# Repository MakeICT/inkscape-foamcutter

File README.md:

MakeICT Foam Cutter Serial Export tool for Inkscape
===================================================

This is an Inkscape extension that allows you to export your Inkscape drawings as G-Code through a serial port.

This project is a modified version of [http://github.com/martymcguire/inkscape-unicorn](http://github.com/martymcguire/inkscape-unicorn)

Installation
============

Inkscape
--------
Copy the contents of `inkscape/` to your Inkscape `extensions/` folder.
Typical locations include:

* Linux - `/usr/share/inkscape/extensions`
* Windows - `C:\Program Files\Inkscape\share\extensions`
* OS X - `/Applications/Inkscape.app/Contents/Resources/extensions`

You will also need pyserial installed to `inkscape/python/Lib` folder.

Arduino
-------
Upload the Arduino code from the `arduino/` folder. We highly recommend using [Ino Tool](http://inotool.org)

Usage
=====

* Size and locate your image appropriately:
	* It looks like only **px** are supported as the units presently
* Convert all text to paths:
	* Select all text objects.
	* Path > Object to Path.
* Export to serial
	* Extensions > Export > MakeICT Foam Cutter Sender.

Credits
=======

* Marty McGuire pulled this all together into an Inkscape extension.
* [Inkscape](http://www.inkscape.org/) is an awesome open source vector graphics app.
* [Scribbles](https://github.com/makerbot/Makerbot/tree/master/Unicorn/Scribbles%20Scripts) is the original DXF-to-Unicorn Python script.
* [The Egg-Bot Driver for Inkscape](http://code.google.com/p/eggbotcode/) provided inspiration and good examples for working with Inkscape's extensions API.
* Dominic Canare for adding serial code to Marty's original extension
* Tom McGuire for sharing his vast knowledge of G-Code and CNC.

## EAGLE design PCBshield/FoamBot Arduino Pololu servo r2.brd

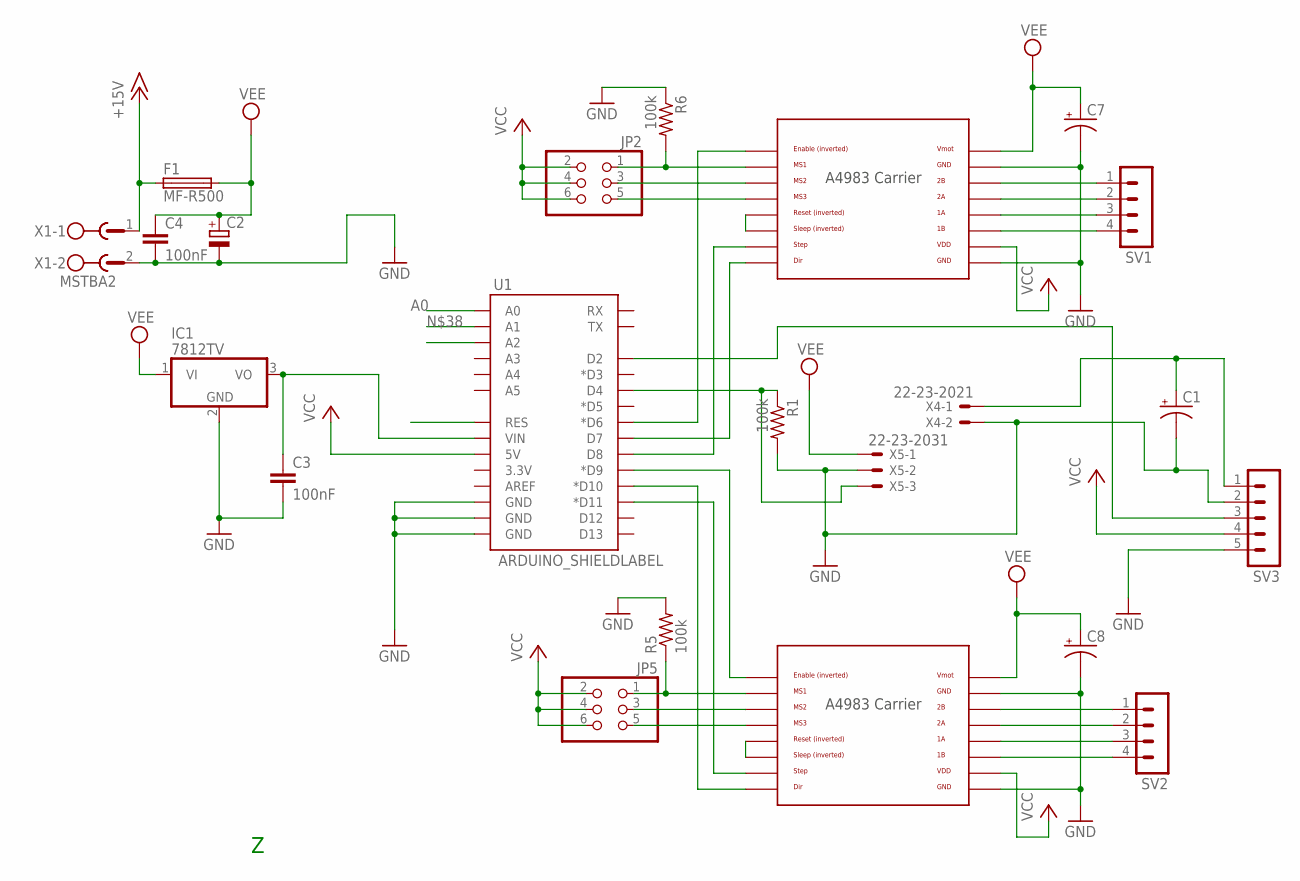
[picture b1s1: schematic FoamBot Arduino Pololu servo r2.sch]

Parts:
C1: CPOL-USE5-10.5; E5-10,5
C2: CPOL-EUE7.5-16; E7,5-16
C3, C4: 100nF; C2.5-3
C7, C8: CAP_POLPTH2; CPOL-RADIAL-10UF-25V
F1: MF-R500; LITTLEFUSE
IC1: 7812TV; TO220V
JP2, JP5: PINHD-2X3; 2X03
R1, R5, R6: 100k; 0207/7
SV1, SV2: MA04-1
SV3: MA05-1
U1: ARDUINO_SHIELDLABEL; DUEMILANOVE_SHIELD
U2, U3: POLOLU_A4983CARRIER; A4983CARRIER
X1: MSTBA2
X4: 22-23-2021
X5: 22-23-2031

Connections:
+15V: F1.1, X1.1
A0: U1.A0
GND: C1.-, C2.-, C3.2, C4.2, C7.2 (-), C8.2 (-), IC1.2 (GND), R1.2, R5.2, R6.1, SV3.2, SV3.5, U1.GND@0 (GND), U1.GND@1 (GND), U1.GND@2 (GND), U2.GND, U2.GND@0 (GND), U3.GND, U3.GND@0 (GND), X1.2, X4.2, X5.2
unnamed: U1.D8, U2.STEP
unnamed: U1.D7, U2.DIR
unnamed: SV1.1, U2.2B
unnamed: SV1.2, U2.2A
unnamed: JP5.1, R5.1, U3.MS1
unnamed: JP5.3, U3.MS2
unnamed: U2.RST, U2.SLP (SLEEP)
unnamed: C3.1, IC1.3 (VO), U1.VIN
unnamed: SV1.3, U2.1A
unnamed: SV1.4, U2.1B
unnamed: SV2.4, U3.1B
unnamed: U1.D6 (*D6), U2.EN
unnamed: JP5.5, U3.MS3
unnamed: JP2.1, R6.2, U2.MS1
unnamed: U1.D11 (*D11), U3.STEP
unnamed: U1.D10 (*D10), U3.DIR
unnamed: JP2.3, U2.MS2
unnamed: JP2.5, U2.MS3
unnamed: U3.RST, U3.SLP (SLEEP)
unnamed: SV2.1, U3.2B
unnamed: SV2.2, U3.2A
unnamed: U1.D9 (*D9), U3.EN
unnamed: R1.1, U1.D4, X5.3
unnamed: SV3.3, U1.D2
unnamed: SV2.3, U3.1A
unnamed: C1.+, SV3.1, X4.1
RESET: U1.RES
VCC: JP2.2, JP2.4, JP2.6, JP5.2, JP5.4, JP5.6, SV3.4, U1.5V, U2.VDD, U3.VDD
VEE: C2.+, C4.1, C7.1 (+), C8.1 (+), F1.2, IC1.1 (VI), U2.VMOT, U3.VMOT, X5.1

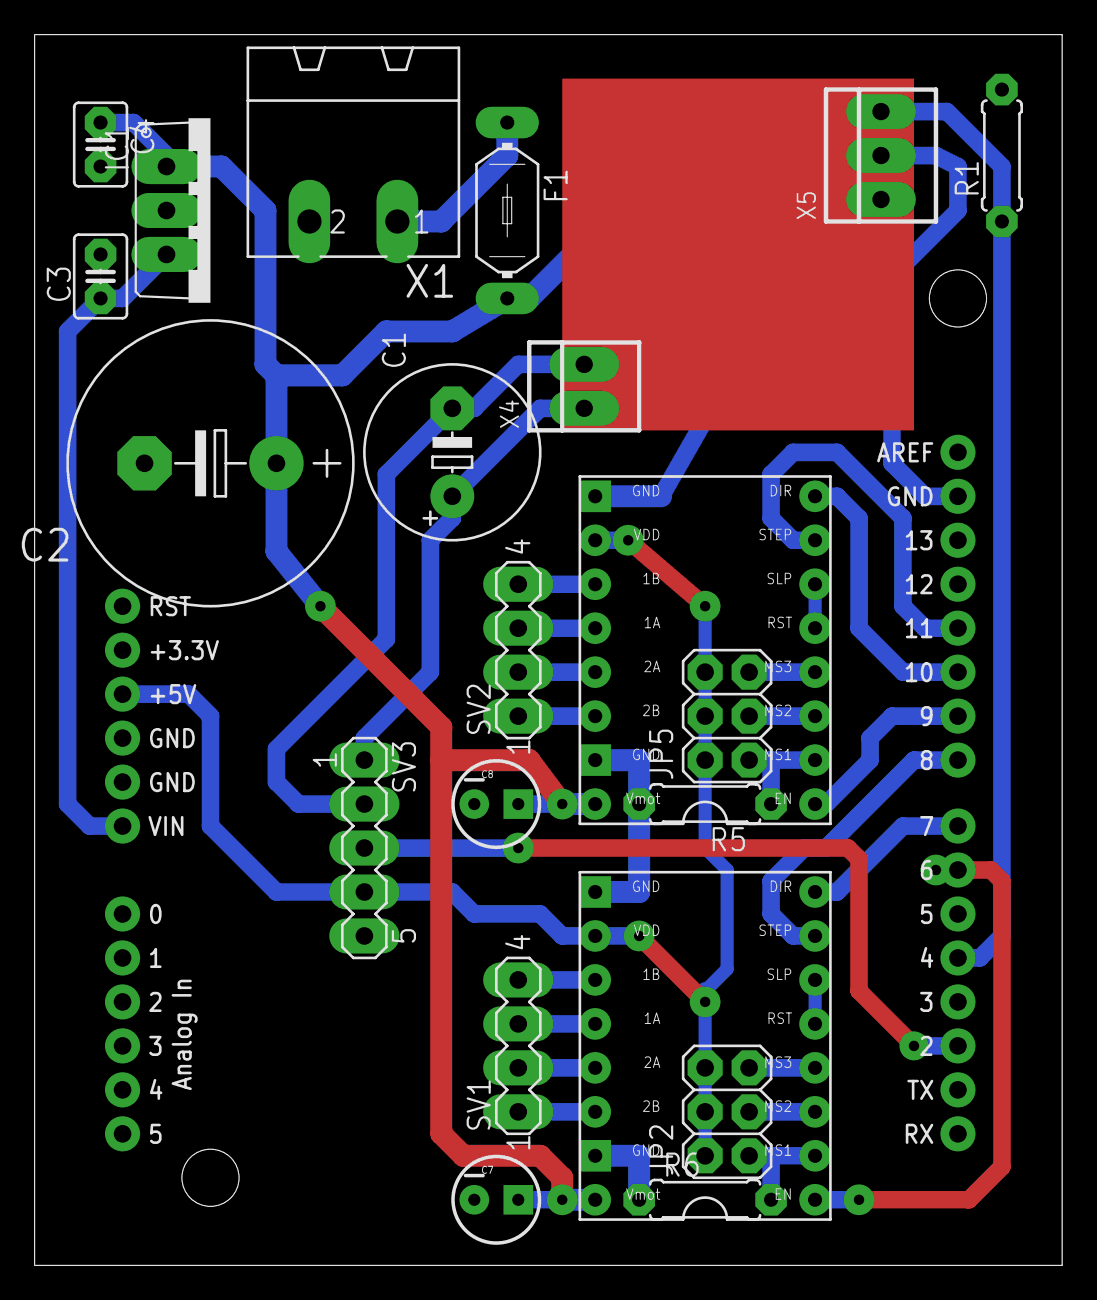
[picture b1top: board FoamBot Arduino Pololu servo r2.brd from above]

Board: 2 copper layers, 59.4 x 71.1 mm, 22 parts (0 on the bottom side), 30 nets.

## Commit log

2015-07-07 Update for serial export
2015-07-07 Accept more units
2015-08-03 Update unicorn.inx
    Name change
2015-08-03 Wait for bits to read
2015-08-30 fix serial com
2015-08-30 cleanup sweep 1
2015-08-30 reformat arduino code
2015-08-30 cleanup
2015-08-30 fix arduino ready code
2015-08-30 spaces to tabs
2015-08-30 fix units bug
2015-09-01 don't send servo off command
2015-10-09 update defaults for foam-cutter
2015-10-09 test scaling and rename y-stepper motor
2015-10-09 formatting
2015-10-09 add manual controls
2015-10-09 fix homing and x-direction. start to fix spindle enable
2015-10-10 fix scaling and spindle
2015-10-10 button color when not at home
2015-10-10 autoconnect
2015-10-10 add opacity-to-depth
2015-10-10 ui layout
2015-10-10 switch to config parser
2015-10-11 Created PCB and Mill files
2015-10-13 cleaned up pcb
2015-10-15 remove popup, show GCODE in debug
2015-10-16 Add progress bar
2015-10-16 add auto connect dialog; move gui pages to separate functions
2015-10-16 add about page
2015-10-16 add gcode buffer, fix layout issues
2015-12-16 disable spindle between cuts
2015-12-24 Add option for curve flatness and fix settings not being applied
2015-12-24 fix opacity angle calc
2015-12-24 make window bigger
2015-12-24 don't die on missing style pair data
2015-12-24 add pause and stop buttons
2015-12-24 stop when window closed
2016-01-17 convert all objects to paths before processing
2016-01-17 show window to hide inkscape object->path processing
2016-01-17 need threading
2016-02-05 ignore objects that have 0 opacity
2016-02-05 hide the 'Please Wait...' window
2016-02-06 window hiding wasn't working, but now it is
2016-02-06 add title
2016-02-06 disconnect serial port when window is closed
2016-02-06 skip unfilled/unstroked things as well
2017-02-08 make it mostly work on windows
2017-02-08 change defaults for MakeICT; allow cm units
2017-02-08 make it work on Linux and .91 again
2017-02-17 remove sleep - why was this here? I hope this still works in Windows

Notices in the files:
parts and their libraries:
SparkFun-Boards: Licensing: CC v3.0 Share-Alike You are welcome to use this library for commercial purposes.
